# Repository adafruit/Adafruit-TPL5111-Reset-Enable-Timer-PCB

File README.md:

## Adafruit TPL5111 Reset Enable Timer PCB

<a href="http://www.adafruit.com/products/3573"><br/>
Click here to purchase one from the Adafruit shop</a>

PCB files for the Adafruit TPL111 Reset Enable Timer. For more details, Pick up one today & check out the product page at
* https://www.adafruit.com/products/3573

### Description

With some development boards, low power usage is an afterthought. Especially when price and usability are the main selling points. So what should you do when it's time to turn around and make that project of yours run on a battery or solar? Sure you could try to hot-air that regulator off, or you could jerry-rig a relay. Or, use a 555? Ugh, the options aren't that great.

The Adafruit TPL5111 Low Power Reset Timer is a stand-alone breakout that will turn any electronics into low-power electronics! It will take care of enabling & disabling your electronics using a built in timer that can vary from once-every 100ms up to once every two hours. Basically, the TPL will set an enable pin high periodically, adjustable by potentiometer or resistor, and turn on your project's power. It will then wait until a signal is received from the project to tell the TPL that it can safely disable the project by setting the enable pin low. If the TPL does not receive a signal by the set time-out, it will reset the device like a watchdog timer.

We also have a TPL5110 breakout, which rather than setting an enable pin high/low, connects and disconnects power. The TPL5111 breakout is best when you have an enable pin you can control, the TPL5110 is best when you are able to 'break' the power input line to place the TPL5110 between the power supply and Vin.

Usage is easy. First, set your desired delay but adjusting the on-board trim pot: all the way to the left is once-per-100ms and all the way to the right is once-every-2-hours. Then, connect VDD up to your 3-5V project power supply, and then your project's enable pin to the Enable pin. Finally, select a signal pin from your project to the Done pin. In your project's code or design, just make sure that it sets the Done pin high once it is completed with its task. That's it!

While the TPL5111 is running (but the remainder of the project is de-powered) the current draw is about 20uA (according to our Monsoon Power Meter).

If you want to turn the device on by hand, you can also activate the TPL by pressing the onboard tactile switch (or wire your own switch to the Delay pin) See? Your power problems just got solved!

Comes as a fully assembled breakout board with a TPL5111 chip, all components on-board, and some header. A little light soldering is required to put it together for breadboard use.

### License

Adafruit invests time and resources providing this open source design, please support Adafruit and open-source hardware by purchasing products from [Adafruit](https://www.adafruit.com)!

Designed by Limor Fried/Ladyada for Adafruit Industries.

Creative Commons Attribution/Share-Alike, all text above must be included in any redistribution. See license.txt for additional details.

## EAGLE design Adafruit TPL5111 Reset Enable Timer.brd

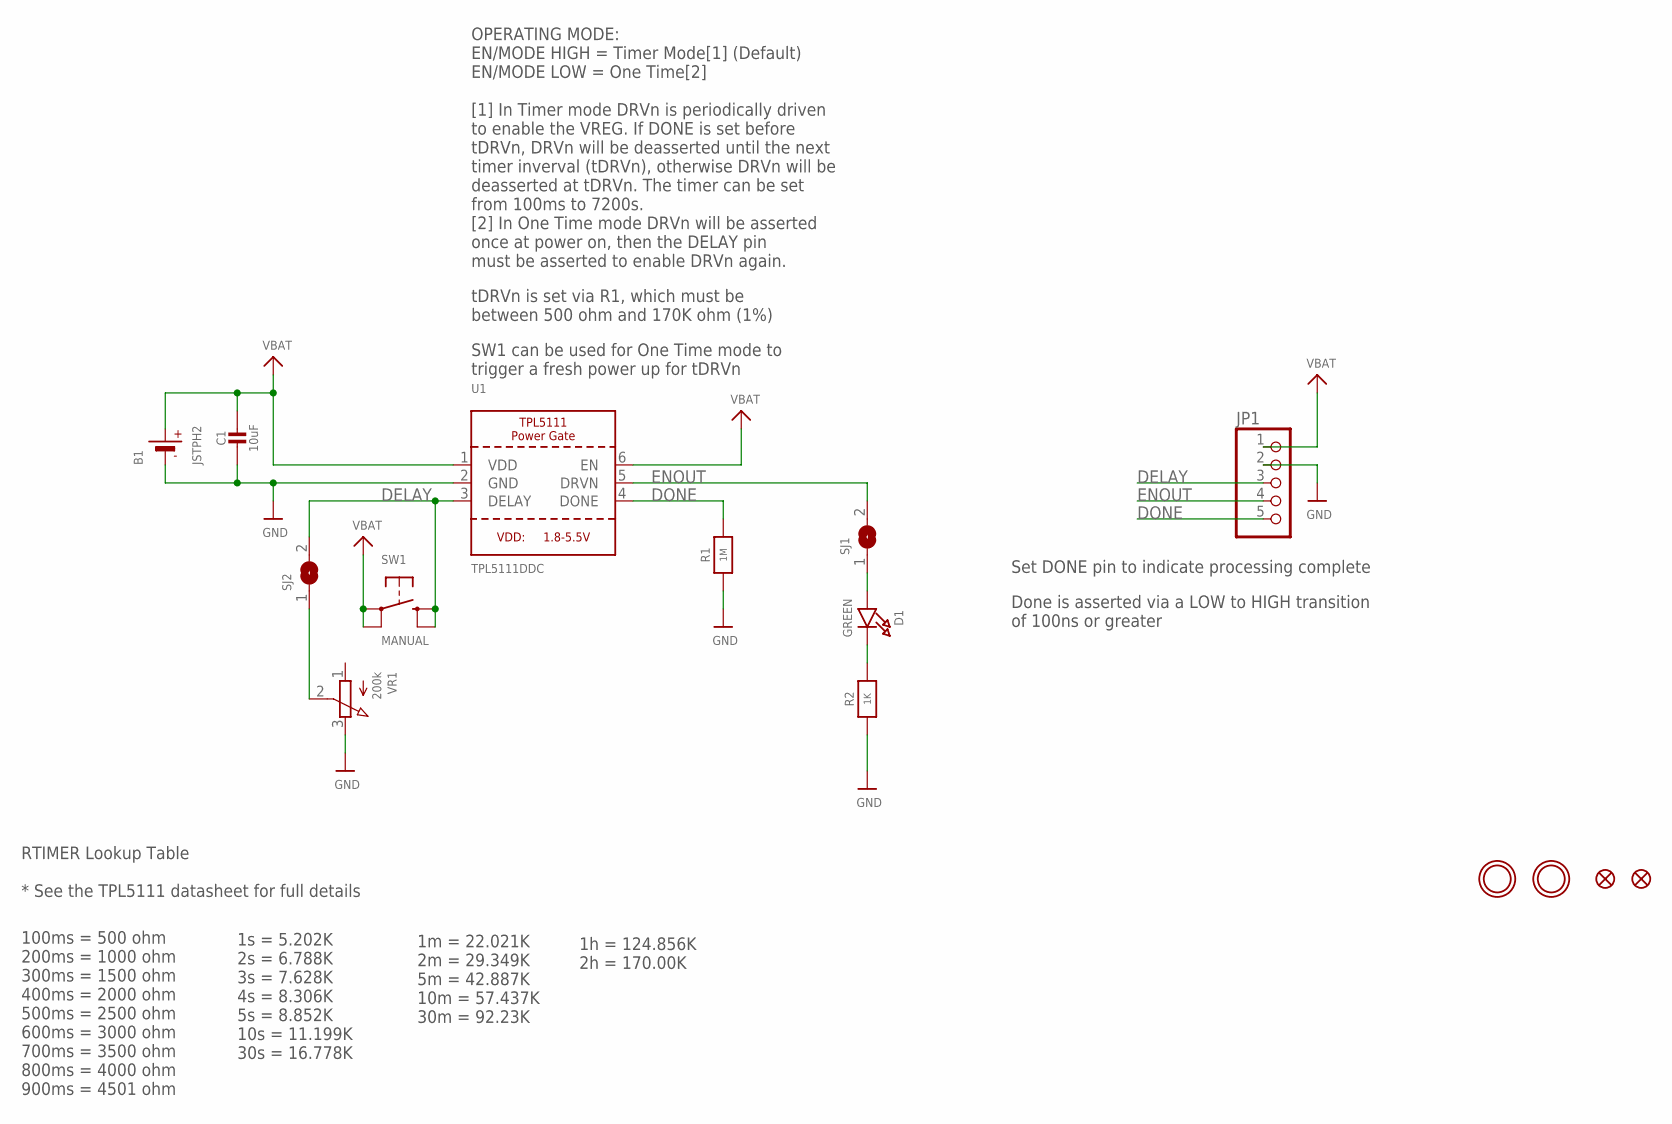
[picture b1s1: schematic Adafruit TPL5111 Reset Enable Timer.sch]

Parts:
B1: JSTPH2
C1: 10uF; 0805-NO
D1: GREEN; CHIPLED_0805_NOOUTLINE
FID2, FID3: FIDUCIAL_1MM
JP1: HEADER-1X576MIL; 1X05_ROUND_76
R1: 1M; 0805-NO
R2: 1K; 0805-NO
SJ1, SJ2: SOLDERJUMPERCLOSED; SOLDERJUMPER_CLOSEDWIRE
SW1: MANUAL; EVQ-Q2_SMALLER
U1: TPL5111DDC; SOT23-6
U$8, U$9: MOUNTINGHOLE2.5; MOUNTINGHOLE_2.5_PLATED
VR1: 200k; TRIMPOT_BOURNS_TC33X-2

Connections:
DELAY: JP1.3, SJ2.2, SW1.B (S), SW1.B' (S1), U1.3 (DELAY)
DONE: JP1.5, R1.2, U1.4 (DONE)
ENOUT: JP1.4, SJ1.2, U1.5 (DRVN)
GND: B1.1 (-), C1.2, JP1.2, R1.1, R2.1, U1.2 (GND), VR1.3 (E)
unnamed: SJ2.1, VR1.2 (S)
unnamed: D1.A, SJ1.1
unnamed: D1.C, R2.2
VDD: B1.2 (+), C1.1, JP1.1, SW1.A, SW1.A' (P1), U1.1 (VDD), U1.6 (EN)

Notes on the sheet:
OPERATING MODE: EN/MODE HIGH = Timer Mode[1] (Default) EN/MODE LOW = One Time[2] [1] In Timer mode DRVn is periodically driven to enable the VREG. If DONE is set before tDRVn, DRVn will be deasserted until the next timer inverval (tDRVn), otherwise DRVn will be deasserted at tDRVn. The timer can be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
Set DONE pin to indicate processing complete
Done is asserted via a LOW to HIGH transition of 100ns or greater
tDRVn is set via R1, which must be between 500 ohm and 170K ohm (1%)
SW1 can be used for One Time mode to trigger a fresh power up for tDRVn
RTIMER Lookup Table * See the TPL5111 datasheet for full details
100ms = 500 ohm 200ms = 1000 ohm 300ms = 1500 ohm 400ms = 2000 ohm 500ms = 2500 ohm 600ms = 3000 ohm 700ms = 3500 ohm 800ms = 4000 ohm 900ms = 4501 ohm
1s = 5.202K 2s = 6.788K 3s = 7.628K 4s = 8.306K 5s = 8.852K 10s = 11.199K 30s = 16.778K
1m = 22.021K 2m = 29.349K 5m = 42.887K 10m = 57.437K 30m = 92.23K
1h = 124.856K 2h = 170.00K

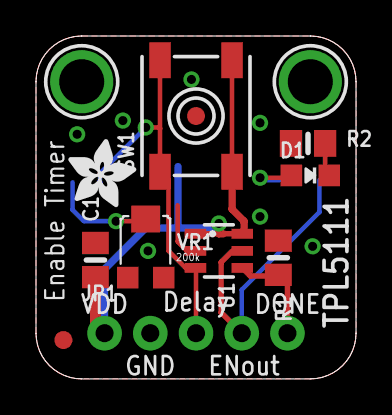
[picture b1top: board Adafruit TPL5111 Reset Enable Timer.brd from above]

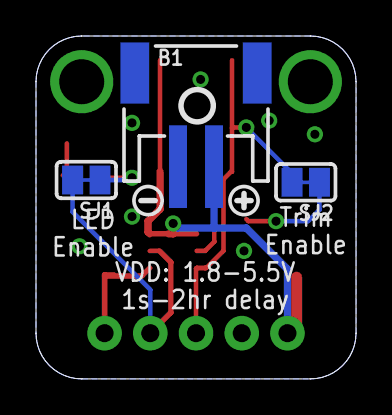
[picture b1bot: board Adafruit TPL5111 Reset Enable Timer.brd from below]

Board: 2 copper layers, 17.8 x 19.1 mm, 19 parts (6 on the bottom side), 8 nets.

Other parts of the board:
U$10: ADAFRUIT_3.5MM
U$11: SYMBOL_PLUS
U$12: SYMBOL_MINUS
U$15: PCBFEAT-REV-040

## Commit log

2017-08-16 init

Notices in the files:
parts and their libraries:
microbuilder: This work is placed in the public domain, and may be freely used for commercial and non-commercial work with the following conditions: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
